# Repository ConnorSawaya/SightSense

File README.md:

# SightSense

A smart guide cane for people who are blind or have low vision. You say where you want to go ("guide me to the apple", "take me to the door"), and a small wheel at the tip of the cane steers you there while avoiding obstacles.

Built at the UCSC AI Hackathon @ SF Tech Week, October 10–11, 2026, for the ASUS Local AI track, where it placed 1st overall.

> Experimental prototype. It does not replace a white cane or a guide dog, and it has not been tested with blind users.

## See it in 3D

**[Open the interactive model and guided tour](https://connorsawaya.github.io/SightSense/)** (or click the picture): drag to turn it, step through each part, and point at a data line to see what it carries. There is more on the [project page](https://connors.dev/sightsense).

| | |
| --- | --- |
|  |  |
| **The wireless links.** Camera frames go from the phone to the GX10, guidance comes back, and one word goes to the Pi. | **The wheel end.** Battery, 5 V converter, motor driver, gearmotor and the 85 mm omni wheel. |
|  |  |
| **Pi to driver.** The six signal wires from the Pi's header to the IBT-2. | **Phone mount.** The iPhone in its tilting cradle, camera forward. |

These are pictures of a CAD model, not photos of the cane. The model was drawn on October 12, after the event, from the printable parts in [`hardware/`](hardware/) and the wiring in [`hardware/wiring.md`](hardware/wiring.md). The bought parts in it are drawn from published sizes, not measured, and where the motor driver, converter and adapter sit is made up: no mount is designed for them yet. It shows three tubes; [`hardware/assembly/`](hardware/assembly/) draws four.

## Photos from the event

Taken by the team at the event.

| | |
| --- | --- |
|  |  |
| The cane at the event, with the wheel end on the floor. | The team: Viraj Rungta, Aryan Kulkarni and Connor Sawaya. Not pictured: Anshuman Kumar. The name tags were added afterwards. |

| | | | |
| --- | --- | --- | --- |
|  |  |  |  |
| The whole cane in hand: handle, phone mount and wheel. | The wheel end on the floor, with tape over the tube joints. | The Raspberry Pi in its case, the jumper wires, the green power adapter and the battery underneath. | The battery pack, the carbon tube and the omni wheel. |

## How it works

```
iPhone (on the cane)        ASUS GX10 (on the table)           Raspberry Pi (on the cane)
camera + LiDAR + position ─► obstacle check, AI models, ─────► drives the wheel motor
        ▲                    route following                    │
        └── beeps and speech ◄──────┘                           ▼
                                                          mecanum wheel
```

1. The iPhone sends a picture, a LiDAR distance map and its position about 15 times a second.
2. The GX10 checks seven directions for clear space and picks the one closest to where you want to go.
3. The GX10 sends one word to the Pi: `LEFT`, `CENTER`, `RIGHT` or `STOP`.
4. The Pi directly drives the mecanum wheel in opposite directions for LEFT/RIGHT. CENTER/STOP/FREE switch it off. If it hears nothing for 0.4 seconds, it switches the motor off.
5. A vision-language model on the GX10 finds named objects, reads signs and answers questions. It never controls the wheel.

AI and guidance run locally on the GX10. The current devices communicate through the existing Tailscale network; a private router was the original plan. Place lookup uses Apple Maps.

## Repository layout

| Folder | What goes here | Owner |
| --- | --- | --- |
| [`contracts/`](contracts/) | The agreed message formats between the phone, the GX10 and the Pi | Everyone |
| [`ios-app/`](ios-app/) | The iPhone app: capture, sending, speech, voice, maps | iPhone app |
| [`gx10/`](gx10/) | Everything that runs on the GX10: receiving frames, obstacle check, AI models, dashboard | GX10 + models, obstacle check |
| [`pi/`](pi/) | The Raspberry Pi motor controller | Cane + Pi |
| [`hardware/`](hardware/) | 3D-printable parts, wiring and build notes for the cane | Cane + Pi |
| [`docs/`](docs/) | Project history, tool disclosure and supporting notes | Team lead |

## Hardware

- iPhone 16 Pro (camera, LiDAR, ARKit)
- ASUS Ascent GX10 (borrowed from ASUS for the event)
- Raspberry Pi 5
- 12 V 120 rpm DC worm gear motor driving an 85 mm omni wheel, IBT-2 (BTS7960) motor driver. Older notes here call it the mecanum wheel
- 12 V 3 Ah battery pack, fuse, kill switch
- 18 mm carbon-fibre tube cane with a printed keyed coupler (see [`hardware/cane-coupler/`](hardware/cane-coupler/))

The full list, down to the screws, is in [`hardware/BOM.md`](hardware/BOM.md).

## Status

**Since the hackathon (October 14):** the GX10 was borrowed for the event and is no longer part of the plan. The iPhone will run the obstacle check itself, a new circuit board on the cane ([`hardware/cane-board/`](hardware/cane-board/)) replaces the Raspberry Pi and takes commands from the phone over Bluetooth, and the talk button's questions will go to a cloud AI. None of that is built yet; the rest of this page describes the cane as it was at the event.

The iPhone and GX10 application code is in. The Pi has direct wheel mode and a one-time SD installer. Software tests use synthetic phone frames, real local WebSockets and mock GPIO. Actual wheel direction, RPM and updated Pi boot remain physical checks; see [`pi/README.md`](pi/README.md).

## Team

Connor Sawaya, Viraj Rungta, Aryan Kulkarni and Anshuman Kumar.

Roles to be added by the team.

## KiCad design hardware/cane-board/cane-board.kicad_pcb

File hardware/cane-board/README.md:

# Cane board (v0.1)

One circuit board for the cane, to replace the Raspberry Pi 5, its 12 V to 5 V converter, the IBT-2 motor driver, the green screw adapter and the jumper wires. The battery, the motor, the talk button and the kill switch stay off the board and plug into it.

A design, not a finished board. The schematic is drawn and checked, and the 46 × 100 mm board is routed on 4 layers with black solder mask: KiCad's design rules check reports 0 errors and 0 unconnected items, and the board matches the schematic. There is no firmware, and nothing has been ordered, built or tested. Drawn on October 13, 2026, after the event.

The thinking stays off the board. Since October 14 the plan is for the iPhone to run the obstacle check, with no GX10. The board does the Pi's job: it holds a Bluetooth LE link to the phone, turns `LEFT`, `CENTER`, `RIGHT`, `STOP` and `FREE` into motor power, sends the talk button's presses to the phone and reports its health. The commands are the same words as in [`../../contracts/MESSAGES.md`](../../contracts/MESSAGES.md); the Bluetooth format for them is not written yet. Nothing on the board changes for Bluetooth: the ESP32-S3 has it built in.

## What is on it

| Block | Main part | What it does |
| --- | --- | --- |
| Battery in | Barrel jack, resettable fuse that holds 4 A, two AO3401A | Takes the pack's barrel plug. Stays off if the plug is wired the other way round |
| Motor supply | AO3401A | Feeds the motor driver only while the kill-switch loop is closed |
| Motor driver | DRV8876 | Replaces the IBT-2. 3.5 A peak, with a current limit set by one resistor and a current reading for the processor |
| 12 V to 5 V | YLPTEC K7805-1000R3 | A sealed ready-made converter module, soldered in. 1 A, 8 to 36 V in. Chosen over a converter built from parts because its layout is done inside the module |
| 3.3 V | AP2112K-3.3 | Supply for the processor, from the 5 V rail or from the firmware socket. The power switch turns this regulator off |
| Processor | ESP32-S3-WROOM-1-N4 | Replaces the Raspberry Pi. Wi-Fi, two cores, USB built in, 4 MB of flash. No SD card, no operating system |
| Phone socket | TPS2069C, USB-C | Not fitted. Pads only. The 1 A module is too small to feed it; fitting it later needs a bigger converter |
| Firmware socket | USB-C | Loads firmware straight into the processor. Also runs the processor on a desk with no battery |
| Spare | Headers | Wheel encoder (RPM is unmeasured today), I2C, a small buzzer motor for the handle, serial |

## The board

46 × 100 mm, four layers, black solder mask, every part on the top side. Tracks on all four layers with ground poured round them and tied together by about 260 vias. The battery, motor-supply and motor tracks are drawn by hand in `make_route.py`, 0.6 to 1.0 mm wide on the outer layers, and the Freerouting autorouter routes everything else around them. The top edge points up the cane.

- **Top:** the processor, with its aerial along the top edge and nothing beside it. Kill switch, talk button and buzzer plugs on the left, where the wires from the handle arrive. Firmware socket on the right edge.
- **Middle:** 3.3 V, the 12 V to 5 V module, the power switch on the right edge, and the unfitted phone socket's pads.
- **Bottom:** battery jack and motor XT30 socket on the bottom edge, with the fuse, the two protection FETs and the motor driver just above them. The two motor tracks run straight down the underside from the driver to the XT30. Encoder plug on the left.
- Four M3 holes: two just below the processor and two at the bottom corners.

In the pictures four parts are stand-ins of the same kind and size, because KiCad ships no 3D model for the ones chosen: the firmware socket, the two push buttons and the slide switch. The fuse and the XT30 have no model and show as bare pads. The bare pads on the right are the phone socket.

### Checks on the routed board, October 14

- KiCad's design rules check: 0 errors, 0 unconnected items. The board matches the schematic (the only differences are unused pins and part descriptions).
- No copper under the processor's aerial on any of the four layers.
- Battery, motor and 5 V tracks run only on the outer layers.
- Narrowest copper on each motor-current path, pad to pad, checked by script: battery jack to fuse 1.0 mm; fuse to the protection FETs 0.6 mm; FETs to the kill-switch FET 0.8 to 1.0 mm; kill-switch FET to the driver 0.6 to 1.0 mm, then 0.4 mm for the last 1.4 mm into the pin; driver to the XT30 1.0 mm, with 0.4 mm for about 1 mm at each pin. The driver's pins are 0.3 mm wide, so the copper can not be wider there.
- By the IPC-2221 rule of thumb, a 0.4 mm outer track holding 2.2 A all the time would warm by about 35 °C; at the 0.4 to 0.6 A the motor usually takes, about 2 °C. These runs are short and next to large copper, so the real figure should be lower. Estimates, not measurements.
- Ordering files: `export/fab/` holds the Gerbers and drill files zipped for upload, JLCPCB's placement file and the BOM. `export/fab-other/` holds the same board for other assemblers (PCBWay and the like): a BOM by maker's part number, a placement file in KiCad's rotations, and a top assembly drawing. Made by `make_fab.py`.

## Three ways the motor is switched off

None of these depends on the firmware being right.

1. **Kill switch.** A switch on connector J3 holds the motor supply on. Open the switch, unplug it or break a wire, and the motor supply is off, by my sums within about 2 ms. The processor cannot override it. The switch carries about 0.5 mA, so it can be small and its wires thin.
2. **Watchdog.** The driver is awake only while the processor keeps toggling one pin. If the firmware hangs or the processor resets, the driver sleeps: in about 60 ms if the pin stops low, about 125 ms if it stops high (`check_watchdog.py`). Solder jumper JP1 bypasses this if it misbehaves.
3. **Current limit.** R5 sets the motor's current limit: 3.3 V ÷ R5 ÷ 0.001. With 1.5 kΩ that is 2.2 A, set above the 1.0 to 1.7 A stall currents in seller tables so the motor pushes as hard as it did on the IBT-2. That is the steady figure: for about the first millisecond of a pulse, the empty filter capacitor C7 draws on IPROPI through R6 and lets the current reach about 2.5 A (an outside review's estimate). The motor's inductance and the driver's timing set the real peaks; measure them. The IBT-2 has no such limit. Lower it once the stall current is measured.

The firmware still has to keep the rules in `AGENTS.md`: off when a command's time-to-live runs out, off after 0.4 s of silence, and no motor power taken from the network.

### Rules for the firmware

The board's protection assumes these. Each comes from an item in [`POTENTIAL_PROBLEMS.md`](POTENTIAL_PROBLEMS.md).

1. **Toggle HBEAT from the main control loop, as a 200 Hz square wave or faster** (400 toggles a second), and only when the loop has run all the way through. Never from a hardware timer or PWM, which keeps running when the program hangs. `check_watchdog.py` puts nSLEEP at 2.5 V at 200 Hz, 2.2 V at 100 Hz, and below the driver's 1.5 V threshold under about 40 Hz. The driver sleeps about 60 ms after the toggling stops with the pin low, and about 125 ms if it is left high, so the firmware's own stop leaves it low (items 12 and 27).
2. **Stop driving the motor when VBAT_ADC reads under 9.3 V**, and say "battery low" before that. The dividers and their capacitors settle with a 9 ms time constant, so ignore the readings for the first 100 ms after power-up, and calibrate them: battery volts are about 11 times the pin's. Below about 8 V at the jack the 5 V module drops out and the processor resets (item 31).
3. **Back off on a stall.** Read I_ADC with 12 dB attenuation: Espressif characterises that range to 2.9 V, about 1.93 A at 1.5 V per amp, so treat anything above it as high current. When it stays high for longer than a pulse, stop and wait. At the 2.2 A limit the driver makes about 3.4 W and its own over-temperature cut-out will stop it anyway (item 22).
4. **Treat nFAULT low as "motor off until it clears".** It reports overcurrent, undervoltage and over-temperature, not the normal 2.2 A chopping (item 28).
5. **Arm in order.** At boot set MOT_EN, HBEAT and the buzzer low before anything else. Start the heartbeat, then keep MOT_EN low for about 15 ms before driving. The model fills the pump in under 1 ms and the driver wakes in 1 ms, but capacitor tolerances can slow the pump several times over (an outside review). The driver's inputs are pulled down and the pump is empty at power-up, so this is belt and braces.
6. **Disarm at once.** On a stale command, a lost link or any fault: MOT_EN low straight away, heartbeat stopped low, and wait for a fresh command after re-arming.

The kill switch does not protect against its two wires shorting together. That reads as "switch closed".

**Brake or coast.** With PMODE on ground the driver runs in PH/EN mode. When the firmware turns the motor off, the driver brakes it (both low-side switches on); when the driver sleeps, through the watchdog or a hang, the motor coasts. The IBT-2 on the Pi coasted, because the Pi switched its enables off. The motor's worm gear holds the wheel either way, so the two differ only in the last few milliseconds of spin-down, and a brake ends each pulse sooner. Decided on October 14 to keep it. Firmware that wants a coast for `FREE` stops toggling the heartbeat low, and the driver sleeps within about 60 ms.

## Will it run for three hours?

By these sums, yes, with a lot to spare. The phone is not powered from the board: the decision on October 13 was to leave the phone socket's parts off.

Every figure here is an estimate. Nothing was measured.

| What | Power from the battery | How I got it |
| --- | --- | --- |
| Processor, lights, standby | About 0.8 W | 120 mA at 3.3 V assumed with Wi-Fi held open. Espressif gives 95 mA receiving and 355 mA peaks sending, but no average |
| Motor, typical | About 1.3 W | Assumes the wheel drives 30% of the time at 0.4 A |
| Motor, driving all the time | About 6.6 W | 0.6 A, the highest rated current in the seller tables |
| Phone socket at full rate, if it is ever fitted | About 8.5 W | 7.5 W at the socket, plus converter loss |

The pack is labelled 12 V 3 Ah, about 32 Wh. I counted 26 Wh as usable. Its capacity has not been checked under load.

| Case | Power | Runs for |
| --- | --- | --- |
| Typical | 2.1 W | About 12 hours |
| Wheel driving all the time | 7.4 W | About 3.5 hours |
| If the socket is fitted: typical, and the phone taking 4.5 W | 7.2 W | About 3.5 hours |
| If the socket is fitted: typical, and the phone taking the full 7.5 W | 10.6 W | About 2.5 hours |

- The Raspberry Pi 5 idles at about 3 W with Wi-Fi on, so the processor's share drops to roughly a quarter.
- The phone runs on its own battery, about 13.6 to 13.9 Wh, and is likely to run out before the cane does. How much the app draws is not measured.
- The socket can no longer be fitted as it is: the 1 A module is too small for it, so a bigger converter would be needed first. If that is done, a 5 Ah pack of the same kind would cover every row above. Whether an iPhone takes 1.5 A from it is not confirmed; the socket advertises 1.5 A the standard way, with 22 kΩ on each CC pin.

## Currents against the parts' ratings

| Path | Most it can carry by design | Part's rating |
| --- | --- | --- |
| Battery jack, fuse, reverse-plug FETs | About 2.5 A: motor at its 2.2 A limit and the processor's peaks, on a 9 V pack | Jack 5 A, fuse holds 4 A, two FETs of 4 A each side by side |
| Kill-switch FET | 2.2 A, the motor's limit. About 0.3 W of heat then, an estimated 35 °C rise. R2 and R3 hold its gate at 0.43 of the battery: 3.9 V from a flat 9 V pack, 10.6 V at the protection diode's clamp | 4 A |
| Motor driver | 2.2 A, set by R5 | 3.5 A peak |
| 5 V rail | About 0.5 A, the processor's peaks | 1 A |
| 3.3 V rail | About 0.44 A: 355 mA Wi-Fi peak and an 80 mA buzzer | 0.6 A |

- The motor's stall current is 1.0 to 1.7 A in seller tables for JGY-370 motors. None of those tables is for the team's motor. Measure it, then choose R5.
- A stalled motor at 1.7 A makes the driver turn about 2 W into heat (0.7 Ω, two switches in series); at the 2.2 A limit, about 3.4 W. Either is too hot to last; the driver's own over-temperature cut-out switches it off, and the firmware should stop on a stall. At 0.4 to 0.6 A it is 0.1 to 0.25 W.
- On the Pi the IBT-2 ran the motor at 70 to 100% power with no limit at all, so the 2.2 A limit should not take away push the motor had.

## Processor pins

| ESP32 pin | Net | Job |
| --- | --- | --- |
| IO1 | `I_ADC` | Motor current, 1.5 V per amp with R5 at 1.5 kΩ. Reads up to about 2 A |
| IO2 | `VBAT_ADC` | Battery voltage ÷ 11 (1M and 100k): 1.15 V at a full pack |
| IO4 | `VM_ADC` | Motor supply ÷ 11. Tells the firmware whether the kill switch is closed |
| IO5 | `MOT_EN` | Motor power (PWM) |
| IO6 | `MOT_PH` | Motor direction |
| IO7 | `HBEAT` | Watchdog: must keep toggling |
| IO8, IO9 | `SDA`, `SCL` | I2C header |
| IO10 | `HAPTIC` | Buzzer motor |
| IO11 | `PH_EN` | Phone socket on (high) or off. Spare while the socket is not fitted |
| IO12 | `PH_FLT` | Phone socket overloaded (low). Spare while the socket is not fitted |
| IO13, IO14 | `ENC_A`, `ENC_B` | Encoder header |
| IO15 | `DRV_FLT` | Motor driver fault (low) |
| IO16 | `TALK` | Talk button (low when pressed) |
| IO21 | `LED_ST` | Status light |
| IO19, IO20 | `USB_DN`, `USB_DP` | Firmware socket |

The current, battery and motor-supply readings use ADC1, which works with Wi-Fi on. The motor pins only glitch low at power-up, by Espressif's table, and the driver is asleep then anyway.

## Connectors

| Ref | For | Type |
| --- | --- | --- |
| J1 | Battery | Barrel jack for a 5.5 mm plug, 2.0 mm pin. Measure the pack's plug before ordering: a 2.5 mm plug will be loose, and the same jack comes with a 2.5 mm pin |
| J2 | Motor | XT30 socket, upright. Solder the motor wires to a matching XT30 plug; nothing is soldered to the board. Which wire goes to which pin only sets the wheel's direction, which the firmware can swap, as `--swap` does on the Pi |
| J3 | Kill switch | JST XH, 2 way. Fit a jumper if there is no switch |
| J4 | Talk button | JST XH, 2 way. The 10 kΩ pull-up `wiring.md` suggests for a long wire is on the board |
| J5 | Wheel encoder | JST XH, 4 way: 3.3 V, ground, A, B |
| J6 | I2C | Pin header, 4 way |
| J7 | Buzzer motor | JST XH, 2 way, 3.3 V |
| J8 | Serial | Pin header, 3 way |
| J10 | Phone power | USB-C, power only. Not fitted |
| J11 | Firmware | USB-C |

## Cost

[`BOM.md`](BOM.md) has every line with its order code, price and JLCPCB class, read from JLCPCB's parts library on October 13, 2026.

- Parts for one board: $10.48. The processor module is $4.13 of that.
- Five boards made and assembled by JLCPCB, 4 layers, black: $107.31 before shipping, duty and tax; about $172 delivered with the 35% tariff, so about $34 a board. See [`COST.md`](COST.md).
- The BOM lists the changes that cut the cost and what each one changed in the design.
- Bench-test parts to buy first: a DRV8876 breakout at $8.15 and an ESP32-S3 dev board at about $15 to $20.
- Not priced: the kill switch and the plug leads.

What the board replaces is not priced in this repository. My guess for a Raspberry Pi 5 with cooler, case and card, the converter and the IBT-2 is $100 to $120.

## Files

| File | What it is |
| --- | --- |
| `make_board.py` | Lists every part and the net on every pin, draws the schematic from that, and checks it. Standard-library Python; needs KiCad 10 |
| `cane-board.kicad_sch`, `cane-board.kicad_pro` | The KiCad 10 project. Open it in KiCad to look or to carry on by hand |
| `cane-board.kicad_sym`, `sym-lib-table` | The DRV8876 symbol, which KiCad does not ship |
| `make_pcb.py` | Places every part on the board from a table of positions, joins the pads to their nets, runs KiCad's design rules check and renders the 3D pictures. Run it with the Python inside KiCad |
| `make_route.py` | Lays the hand-drawn power tracks, runs the Freerouting autorouter for the rest, widens what it can, pours and stitches ground, makes the board black and runs the design rules check. Needs Java and the Freerouting jar in `FREEROUTING_JAR` |
| `make_fab.py` | Writes the ordering files in `export/fab/` and `export/fab-other/`. JLCPCB's placement file has each part's pad centre and JLCPCB's rotation, checked part by part and in JLCPCB's placement viewer. Run it with the Python inside KiCad |
| `check_watchdog.py` | Simulates the watchdog pump: nSLEEP voltage against the heartbeat rate, and the time to sleep. Standard-library Python |
| `cane-board.kicad_pcb` | The routed board |
| `export/cane-board.pdf` | The schematic to read or print |
| [`BOM.md`](BOM.md) | What to buy, with order codes and prices, and what the board lets you drop |
| `export/parts.csv` | The board's parts grouped into lines to buy |
| `export/bom-jlcpcb.csv` | The fitted parts in the columns JLCPCB's assembly order form reads |
| `previews/cane-board.png` | Picture of the PDF, made separately |
| `previews/board-*.png` | 3D pictures of the board, rendered by KiCad |

`python3 make_board.py` rewrites the schematic, so edits made in KiCad are lost. Either change the script, or stop running it once the schematic is being drawn by hand.

Schematic checks on the last run, October 14: 256 pins on 56 nets all on the net the script lists, as read back from KiCad's own netlist; every pin has a matching pad on its footprint; KiCad's electrical rules check reports 0 errors and 0 warnings. These show the drawing matches the list. They do not show the circuit works.

## Not done

- **The link.** Decided October 14: Bluetooth LE from the phone, so no Wi-Fi network or Tailscale is needed (an ESP32 cannot run Tailscale). The message format over it is not written; it belongs in `contracts/MESSAGES.md`, which needs Connor's say-so.
- **Firmware.** Not started. Arduino / PlatformIO (decided October 14). It has to do what `pi/cane.py` and `pi/wheel_drive.py` do, with the same limits and tests run against fakes, plus the rules above.
- **A new electronics mount** for the 46 × 100 mm board.
- **Measurements this design leans on:** the motor's stall and running current, the battery's real capacity, the phone's draw, and the size and polarity of the pack's plug.
- **Try it on bought boards first.** An ESP32-S3 dev board and a DRV8876 breakout would prove the firmware and the motor numbers before any board is ordered.
- Small things known to be rough: the watchdog is simulated (`check_watchdog.py`) but not built, and the kill-switch timing and the gate resistors that replaced the zeners are worked out on paper only; and if the phone socket is ever fitted, it has 5 V on it whenever it is switched on, not only when a phone is attached.

## Where the facts come from

Looked up on October 13 and 14, 2026.

- DRV8876 pins, modes, current-limit formula, capacitors and land pattern: TI datasheet SLVSDS7B.
- K7805-1000R3 pins (1 in, 2 ground, 3 out), 8 to 36 V in, 1 A out: YLPTEC datasheet, read October 14.
- XT30UPB-F: AMASS drawing via KiCad's footprint and the LCSC listing C108769.
- TPS2069C enable polarity and limits: TI datasheet SLVSAU6I. AP2112K: Diodes DS39724.
- AO3401A (30 V, 4 A, gate limit ±12 V, under 85 mΩ with 2.5 V on the gate, 125 °C/W): Alpha & Omega datasheet rev. 3.1.
- Every part's price, stock and class: JLCPCB's parts library, read on October 13, 2026.
- ESP32-S3-WROOM-1 pins, boot pins, power-up glitches, ADC and currents: Espressif module datasheet v1.8 and chip datasheet v2.2.
- USB-C pull-up values: Microchip AN1953, table 6, quoting the USB Type-C specification.
- Motor currents: an OzRobotics JGY-370B table and a Seeed/Aslong sheet. No table for a 120 rpm JGY-370 could be fetched.
- Raspberry Pi 5 idle power: CNX Software's review (3.0 W headless with Wi-Fi) and Jeff Geerling's measurements (2.4 to 3.3 W).
- iPhone 16 Pro battery: 3,582 mAh from a regulatory filing reported by 9to5Mac. Apple does not publish it.
- Barrel jack (5 A, 2.0 mm pin, hole pattern): XKB's drawing for the DC-005-5A-2.0.
- Symbols and footprints other than the DRV8876: KiCad 10's own libraries.

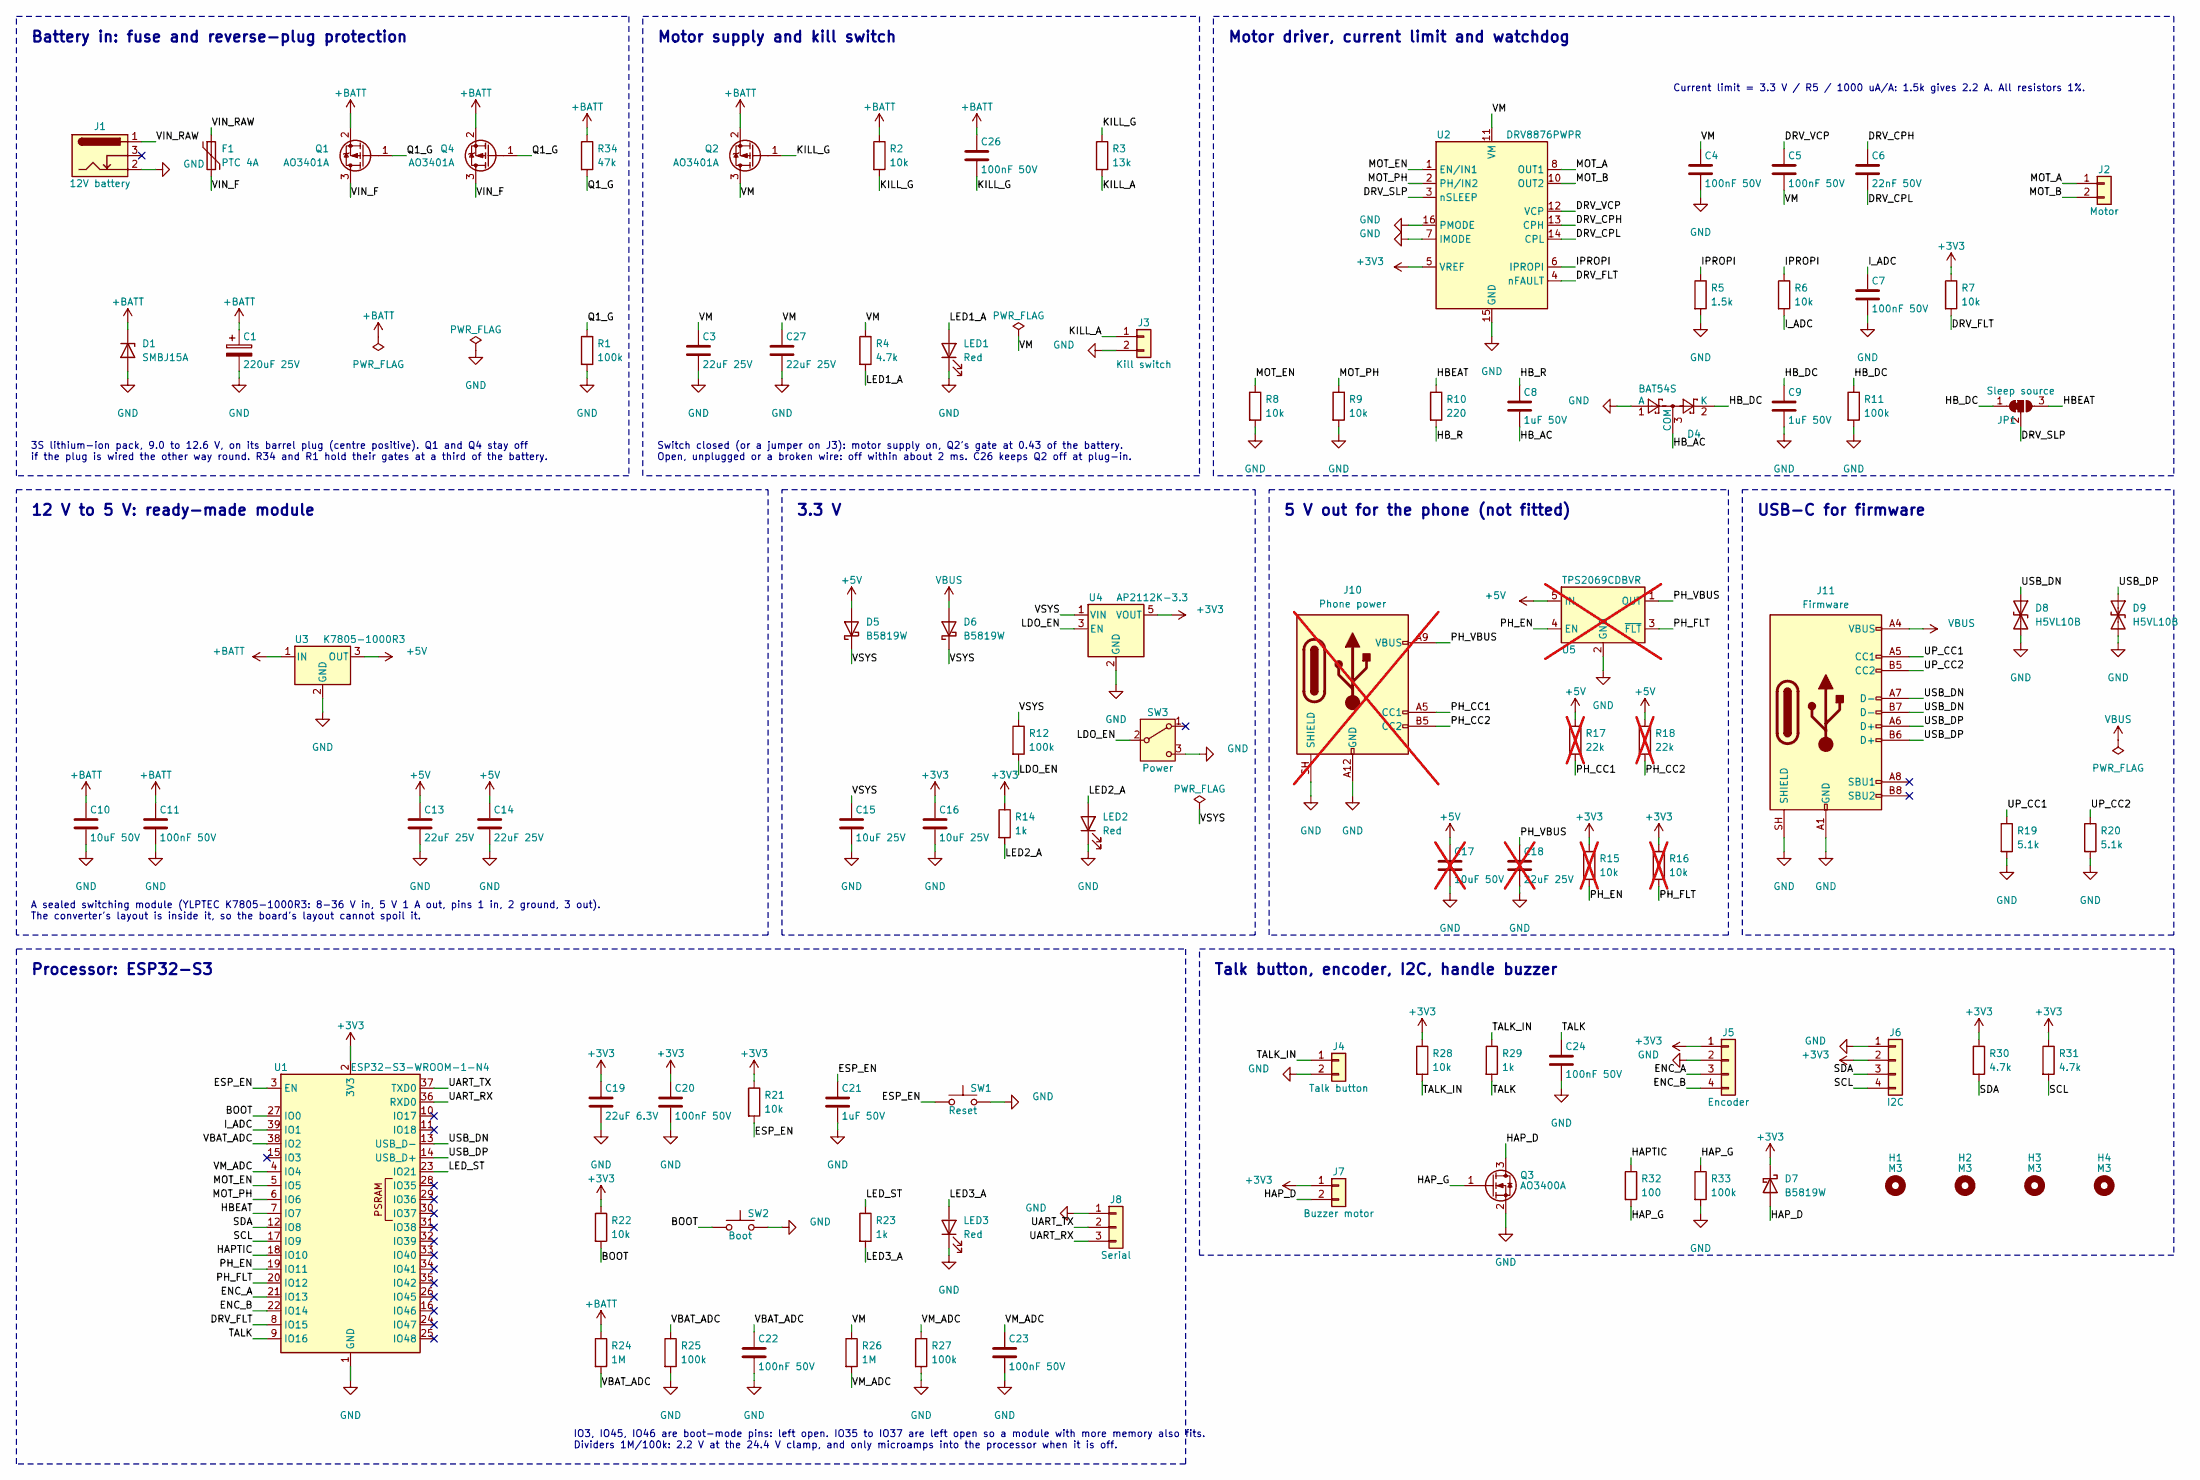
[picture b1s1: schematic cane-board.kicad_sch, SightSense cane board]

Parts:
C1: 220uF 25V; CP_Elec_8x10; MPN EMK1EM221FB0D00R; LCSC C724620
C3, C13, C14, C27: 22uF 25V; C_1206_3216Metric; MPN CL31A226KAHNNNE; LCSC C12891
C4, C5, C7, C11, C20, C22, C23, C24, C26: 100nF 50V; C_0603_1608Metric; MPN CC0603KRX7R9BB104; LCSC C14663
C6: 22nF 50V; C_0603_1608Metric; MPN CL10B223KB8NNNC; LCSC C21122
C8, C9, C21: 1uF 50V; C_0603_1608Metric; MPN CL10A105KB8NNNC; LCSC C15849
C10: 10uF 50V; C_1206_3216Metric; MPN CL31A106KBHNNNE; LCSC C13585
C15, C16: 10uF 25V; C_0805_2012Metric; MPN CL21A106KAYNNNE; LCSC C15850
C17: 10uF 50V; C_1206_3216Metric; MPN CL31A106KBHNNNE; LCSC C13585; not fitted
C18: 22uF 25V; C_1206_3216Metric; MPN CL31A226KAHNNNE; LCSC C12891; not fitted
C19: 22uF 6.3V; C_0603_1608Metric; MPN CL10A226MQ8NRNC; LCSC C59461
D1: SMBJ15A; D_SMB; MPN SMBJ15A; LCSC C19077569
D4: BAT54S; SOT-23; MPN BAT54S; LCSC C7420333
D5, D6, D7: B5819W; D_SOD-123; MPN B5819W; LCSC C8598
D8, D9: H5VL10B; D_SOD-882; MPN H5VL10B; LCSC C7420372
F1: PTC 4A; Fuse_2920_7451Metric; MPN BSMD2920-400-30V; LCSC C20539726
H1, H2, H3, H4: M3; MountingHole_3.2mm_M3
J1: 12V battery; BarrelJack_Horizontal; MPN DC-005-5A-2.0; LCSC C381116
J2: Motor; AMASS_XT30UPB-F_1x02_P5.0mm_Vertical; MPN XT30UPB-F30.G.Y; LCSC C108769
J3: Kill switch; JST_XH_B2B-XH-A_1x02_P2.50mm_Vertical; MPN B2B-XH-A; LCSC C158012
J4: Talk button; JST_XH_B2B-XH-A_1x02_P2.50mm_Vertical; MPN B2B-XH-A; LCSC C158012
J5: Encoder; JST_XH_B4B-XH-A_1x04_P2.50mm_Vertical; MPN B4B-XH-A; LCSC C144395
J6: I2C; PinHeader_1x04_P2.54mm_Vertical; MPN PZ254V-11-04P; LCSC C2691448
J7: Buzzer motor; JST_XH_B2B-XH-A_1x02_P2.50mm_Vertical; MPN B2B-XH-A; LCSC C158012
J8: Serial; PinHeader_1x03_P2.54mm_Vertical; MPN PZ254V-11-03P; LCSC C2937625
J10: Phone power; USB_C_Receptacle_GCT_USB4125-xx-x_6P_TopMnt_Horizontal; MPN USB4125-GF-A; LCSC C3151650; not fitted
J11: Firmware; USB_C_Receptacle_HRO_TYPE-C-31-M-12; MPN TYPE-C-31-M-12; LCSC C165948
JP1: Sleep source; SolderJumper-3_P1.3mm_Bridged12_RoundedPad1.0x1.5mm
LED1, LED2, LED3: Red; LED_0603_1608Metric; MPN KT-0603R; LCSC C2286
Q1, Q2, Q4: AO3401A; SOT-23; MPN AO3401A; LCSC C15127
Q3: AO3400A; SOT-23; MPN AO3400A; LCSC C20917
R1, R11, R12, R25, R27, R33: 100k; R_0603_1608Metric; MPN 0603WAF1003T5E; LCSC C25803
R2, R6, R7, R8, R9, R21, R22, R28: 10k; R_0603_1608Metric; MPN 0603WAF1002T5E; LCSC C25804
R3: 13k; R_0603_1608Metric; MPN 0603WAF1302T5E; LCSC C22797
R4, R30, R31: 4.7k; R_0603_1608Metric; MPN 0603WAF4701T5E; LCSC C23162
R5: 1.5k; R_0603_1608Metric; MPN 0603WAF1501T5E; LCSC C22843
R10: 220; R_0603_1608Metric; MPN 0603WAF2200T5E; LCSC C22962
R14, R23, R29: 1k; R_0603_1608Metric; MPN 0603WAF1001T5E; LCSC C21190
R15, R16: 10k; R_0603_1608Metric; MPN 0603WAF1002T5E; LCSC C25804; not fitted
R17, R18: 22k; R_0603_1608Metric; MPN 0603WAF2202T5E; LCSC C31850; not fitted
R19, R20: 5.1k; R_0603_1608Metric; MPN 0603WAF5101T5E; LCSC C23186
R24, R26: 1M; R_0603_1608Metric; MPN 0603WAF1004T5E; LCSC C22935
R32: 100; R_0603_1608Metric; MPN 0603WAF1000T5E; LCSC C22775
R34: 47k; R_0603_1608Metric; MPN 0603WAF4702T5E; LCSC C25819
SW1: Reset; SW_Push_1P1T_XKB_TS-1187A; MPN TS-1187A-B-A-B; LCSC C318884
SW2: Boot; SW_Push_1P1T_XKB_TS-1187A; MPN TS-1187A-B-A-B; LCSC C318884
SW3: Power; SW_SPDT_Shouhan_MSK12C02; MPN MSK12C02; LCSC C431540
U1: ESP32-S3-WROOM-1-N4; ESP32-S3-WROOM-1; MPN ESP32-S3-WROOM-1-N4; LCSC C2913197
U2: DRV8876PWPR; HTSSOP-16-1EP_4.4x5mm_P0.65mm_EP3.4x5mm_Mask3x3mm_ThermalVi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; MPN DRV8876PWPR; LCSC C575551
U3: K7805-1000R3; Converter_DCDC_RECOM_R-78E-0.5_THT; MPN K7805-1000R3; LCSC C2992391
U4: AP2112K-3.3; SOT-23-5; MPN AP2112K-3.3TRG1; LCSC C51118
U5: TPS2069CDBVR; SOT-23-5; MPN TPS2069CDBVR; LCSC C181752; not fitted

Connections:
+3V3: C16.1, C19.1, C20.1, D7.1 (K), J5.1, J6.2, J7.1, R7.1, R14.1, R15.1, R16.1, R21.1, R22.1, R28.1, R30.1, R31.1, U1.2 (3V3), U2.5 (VREF), U4.5 (VOUT)
+5V: C13.1, C14.1, C17.1, D5.2 (A), R17.1, R18.1, U3.3 (OUT), U5.5 (IN)
+BATT: C1.1, C10.1, C11.1, C26.1, D1.1 (K), Q1.2 (S), Q2.2 (S), Q4.2 (S), R2.1, R24.1, R34.1, U3.1 (IN)
/BOOT: R22.2, SW2.1, U1.27 (IO0)
/DRV_CPH: C6.1, U2.13 (CPH)
/DRV_CPL: C6.2, U2.14 (CPL)
/DRV_FLT: R7.2, U1.8 (IO15), U2.4 (nFAULT)
/DRV_SLP: JP1.2 (C), U2.3 (nSLEEP)
/DRV_VCP: C5.1, U2.12 (VCP)
/ENC_A: J5.3, U1.21 (IO13)
/ENC_B: J5.4, U1.22 (IO14)
/ESP_EN: C21.1, R21.2, SW1.1, U1.3 (EN)
/HAPTIC: R32.1, U1.18 (IO10)
/HAP_D: D7.2 (A), J7.2, Q3.3 (D)
/HAP_G: Q3.1 (G), R32.2, R33.1
/HBEAT: JP1.3 (B), R10.1, U1.7 (IO7)
/HB_AC: C8.2, D4.3 (COM)
/HB_DC: C9.1, D4.2 (K), JP1.1 (A), R11.1
/HB_R: C8.1, R10.2
/IPROPI: R5.1, R6.1, U2.6 (IPROPI)
/I_ADC: C7.1, R6.2, U1.39 (IO1)
/KILL_A: J3.1, R3.2
/KILL_G: C26.2, Q2.1 (G), R2.2, R3.1
/LDO_EN: R12.2, SW3.2 (B), U4.3 (EN)
/LED1_A: LED1.2 (A), R4.2
/LED2_A: LED2.2 (A), R14.2
/LED3_A: LED3.2 (A), R23.2
/LED_ST: R23.1, U1.23 (IO21)
/MOT_A: J2.1, U2.8 (OUT1)
/MOT_B: J2.2, U2.10 (OUT2)
/MOT_EN: R8.1, U1.5 (IO5), U2.1 (EN/IN1)
/MOT_PH: R9.1, U1.6 (IO6), U2.2 (PH/IN2)
/PH_CC1: J10.A5 (CC1), R17.2
/PH_CC2: J10.B5 (CC2), R18.2
/PH_EN: R15.2, U1.19 (IO11), U5.4 (EN)
/PH_FLT: R16.2, U1.20 (IO12), U5.3 (~FLT)
/PH_VBUS: C18.1, J10.A9 (VBUS), J10.B9 (VBUS), U5.1 (OUT)
/Q1_G: Q1.1 (G), Q4.1 (G), R1.1, R34.2
/SCL: J6.4, R31.2, U1.17 (IO9)
/SDA: J6.3, R30.2, U1.12 (IO8)
/TALK: C24.1, R29.2, U1.9 (IO16)
/TALK_IN: J4.1, R28.2, R29.1
/UART_RX: J8.3, U1.36 (RXD0)
/UART_TX: J8.2, U1.37 (TXD0)
/UP_CC1: J11.A5 (CC1), R19.1
/UP_CC2: J11.B5 (CC2), R20.1
/USB_DN: D8.1 (A1), J11.A7 (D-), J11.B7 (D-), U1.13 (USB_D-)
/USB_DP: D9.1 (A1), J11.A6 (D+), J11.B6 (D+), U1.14 (USB_D+)
/VBAT_ADC: C22.1, R24.2, R25.1, U1.38 (IO2)
/VIN_F: F1.2, Q1.3 (D), Q4.3 (D)
/VIN_RAW: F1.1, J1.1
/VM: C3.1, C4.1, C5.2, C27.1, Q2.3 (D), R4.1, R26.1, U2.11 (VM)
/VM_ADC: C23.1, R26.2, R27.1, U1.4 (IO4)
/VSYS: C15.1, D5.1 (K), D6.1 (K), R12.1, U4.1 (VIN)
GND: C1.2, C3.2, C4.2, C7.2, C9.2, C10.2, C11.2, C13.2, C14.2, C15.2, C16.2, C17.2, C18.2, C19.2, C20.2, C21.2, C22.2, C23.2, C24.2, C27.2, D1.2 (A), D4.1 (A), D8.2 (A2), D9.2 (A2), J1.2, J3.2, J4.2, J5.2, J6.1, J8.1, J10.A12 (GND), J10.B12 (GND), J10.SH (SHIELD), J11.A1 (GND), J11.A12 (GND), J11.B1 (GND), J11.B12 (GND), J11.SH (SHIELD), LED1.1 (K), LED2.1 (K), LED3.1 (K), Q3.2 (S), R1.2, R5.2, R8.2, R9.2, R11.2, R19.2, R20.2, R25.2, R27.2, R33.2, SW1.2, SW2.2, SW3.3 (C), U1.1 (GND), U1.40 (GND), U1.41 (GND), U2.7 (IMODE), U2.9 (PGND), U2.15 (GND), U2.16 (PMODE), U2.17 (PAD), U3.2 (GND), U4.2 (GND), U5.2 (GND)
VBUS: D6.2 (A), J11.A4 (VBUS), J11.A9 (VBUS), J11.B4 (VBUS), J11.B9 (VBUS)

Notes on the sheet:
USB-C for firmware
Motor driver, current limit and watchdog
Battery in: fuse and reverse-plug protection
Processor: ESP32-S3
Motor supply and kill switch
3.3 V
3S lithium-ion pack, 9.0 to 12.6 V, on its barrel plug (centre positive). Q1 and Q4 stay off if the plug is wired the other way round. R34 and R1 hold their gates at a third of the battery.
Switch closed (or a jumper on J3): motor supply on, Q2's gate at 0.43 of the battery. Open, unplugged or a broken wire: off within about 2 ms. C26 keeps Q2 off at plug-in.
Current limit = 3.3 V / R5 / 1000 uA/A: 1.5k gives 2.2 A. All resistors 1%.
5 V out for the phone (not fitted)
A sealed switching module (YLPTEC K7805-1000R3: 8-36 V in, 5 V 1 A out, pins 1 in, 2 ground, 3 out). The converter's layout is inside it, so the board's layout cannot spoil it.
IO3, IO45, IO46 are boot-mode pins: left open. IO35 to IO37 are left open so a module with more memory also fits. Dividers 1M/100k: 2.2 V at the 24.4 V clamp, and only microamps into the processor when it is off.
12 V to 5 V: ready-made module
Talk button, encoder, I2C, handle buzzer

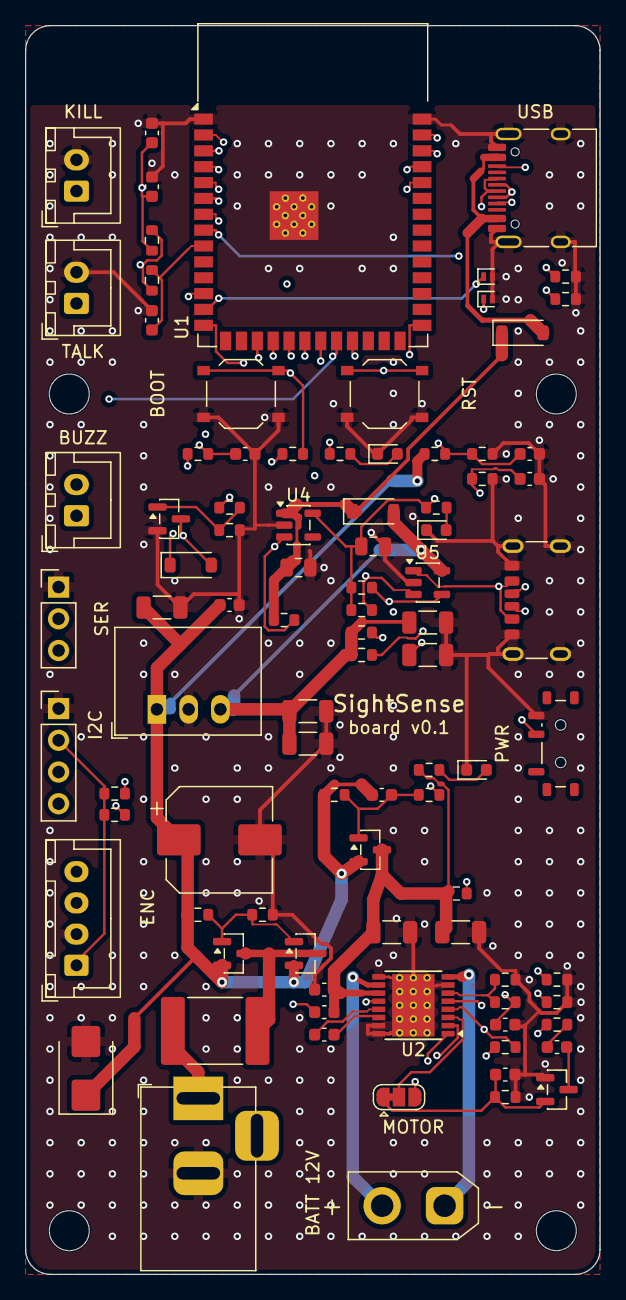
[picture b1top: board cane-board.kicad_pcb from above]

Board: 4 copper layers, 46.0 x 100.0 mm, 95 parts (0 on the bottom side), 56 nets.

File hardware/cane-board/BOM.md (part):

# Cane board: bill of materials

Everything needed to build the cane's electronics around the [cane board](README.md), and what the board lets you drop. The cane's tubes, printed parts and screws are unchanged and stay in [`../BOM.md`](../BOM.md).

Nothing here has been ordered. Order codes, prices, stock and JLCPCB's class for each part were read from JLCPCB's parts library on October 13, 2026, and will drift. Prices are US dollars for one piece, before shipping, duty and tax.

## What changes on the cane

| Item | Cane as built | With the cane board |
| --- | --- | --- |
| Raspberry Pi 5, cooler, case, microSD card | In use | Not needed: the ESP32-S3 on the board does the job |
| Converter, 12 V to 5 V | In use | Not needed: built into the board |
| Motor driver, IBT-2 | In use | Not needed: DRV8876 on the board |
| Barrel-to-screw adapter, six jumper wires | In use | Not needed: the battery plugs into the board |
| Battery, 12 V 3 Ah | In use | Keep |
| Gearmotor and omni wheel | In use | Keep. Solder the two motor wires to an XT30 plug; it plugs into the board |
| Talk button and its two wires | In use | Keep. Needs a 2-way JST XH plug on the board end |
| Kill switch | Not fitted | Buy: a switch for the handle (decided October 14). See section 4 |
| iPhone 16 Pro | In use | Keep. It runs the obstacle check and talks to the board over Bluetooth LE. It runs on its own battery |
| ASUS Ascent GX10 | Used at the hackathon, borrowed | Not needed: dropped from the plan on October 14 |
| Electronics mount (printed) | Holds the Pi and battery | Has to be redrawn for the board |

## 1. On the board

<!-- fitted: written by make_board.py -->
82 parts on 40 lines. The 40 lines with a price come to $10.48 for one board at JLCPCB's price for one piece. 7 lines (9 parts) are through-hole and cost $3.07 of that. JLCPCB classes 23 lines as Basic and 3 as Preferred, which carry no fee; 7 surface-mount lines are Extended and carry its per-line fee.

| Qty | Ref | Part | Package | Maker's number | LCSC | JLCPCB class | Each | Line |
| --- | --- | --- | --- | --- | --- | --- | --- | --- |
| 1 | U1 | ESP32-S3-WROOM-1-N4 | Module | ESP32-S3-WROOM-1-N4 | C2913197 | Extended | $4.130 | $4.13 |
| 1 | U2 | DRV8876PWPR | HTSSOP-16 | DRV8876PWPR | C575551 | Extended | $0.780 | $0.78 |
| 1 | U3 | K7805-1000R3 | Through-hole, 3 pins | K7805-1000R3 | C2992391 | Extended | $2.348 | $2.35 |
| 1 | U4 | AP2112K-3.3 | SOT-23-5 | AP2112K-3.3TRG1 | C51118 | Extended | $0.172 | $0.17 |
| 3 | Q1, Q4, Q2 | AO3401A | SOT-23 | AO3401A | C15127 | Basic | $0.102 | $0.31 |
| 1 | Q3 | AO3400A | SOT-23 | AO3400A | C20917 | Basic | $0.089 | $0.09 |
| 1 | D1 | Diode, SMBJ15A | SMB | SMBJ15A | C19077569 | Preferred | $0.055 | $0.06 |
| 1 | D4 | Diode, BAT54S | SOT-23 | BAT54S | C7420333 | Preferred | $0.014 | $0.01 |
| 3 | D5, D6, D7 | Diode, B5819W | SOD-123 | B5819W | C8598 | Basic | $0.028 | $0.08 |
| 2 | D8, D9 | Diode, H5VL10B | DFN1006 | H5VL10B | C7420372 | Preferred | $0.006 | $0.01 |
| 3 | LED1, LED2, LED3 | LED, Red | 0603 | KT-0603R | C2286 | Basic | $0.008 | $0.02 |
| 1 | F1 | Fuse, PTC 4A | 2920 | BSMD2920-400-30V | C20539726 | Extended | $0.226 | $0.23 |
| 1 | C1 | Capacitor, 220uF 25V | 8 x 10 mm can | EMK1EM221FB0D00R | C724620 | Extended | $0.114 | $0.11 |
| 4 | C3, C27, C13, C14 | Capacitor, 22uF 25V | 1206 | CL31A226KAHNNNE | C12891 | Basic | $0.128 | $0.51 |
| 1 | C6 | Capacitor, 22nF 50V | 0603 | CL10B223KB8NNNC | C21122 | Basic | $0.007 | $0.007 |
| 3 | C8, C9, C21 | Capacitor, 1uF 50V | 0603 | CL10A105KB8NNNC | C15849 | Basic | $0.016 | $0.05 |
| 1 | C10 | Capacitor, 10uF 50V | 1206 | CL31A106KBHNNNE | C13585 | Basic | $0.159 | $0.16 |
| 2 | C15, C16 | Capacitor, 10uF 25V | 0805 | CL21A106KAYNNNE | C15850 | Basic | $0.069 | $0.14 |
| 1 | C19 | Capacitor, 22uF 6.3V | 0603 | CL10A226MQ8NRNC | C59461 | Basic | $0.031 | $0.03 |
| 9 | C26, C4, C5, C7, C11, C20, C22, C23, C24 | Capacitor, 100nF 50V | 0603 | CC0603KRX7R9BB104 | C14663 | Basic | $0.014 | $0.13 |
| 6 | R1, R11, R12, R25, R27, R33 | Resistor, 1%, 100k | 0603 | 0603WAF1003T5E | C25803 | Basic | $0.003 | $0.02 |
| 8 | R2, R6, R7, R8, R9, R21, R22, R28 | Resistor, 1%, 10k | 0603 | 0603WAF1002T5E | C25804 | Basic | $0.005 | $0.04 |
| 1 | R3 | Resistor, 1%, 13k | 0603 | 0603WAF1302T5E | C22797 | Basic | $0.003 | $0.003 |
| 3 | R4, R30, R31 | Resistor, 1%, 4.7k | 0603 | 0603WAF4701T5E | C23162 | Basic | $0.003 | $0.008 |
| 1 | R5 | Resistor, 1%, 1.5k | 0603 | 0603WAF1501T5E | C22843 | Basic | $0.002 | $0.002 |
| 1 | R10 | Resistor, 1%, 220 | 0603 | 0603WAF2200T5E | C22962 | Basic | $0.004 | $0.004 |
| 3 | R14, R23, R29 | Resistor, 1%, 1k | 0603 | 0603WAF1001T5E | C21190 | Basic | $0.002 | $0.006 |
| 2 | R19, R20 | Resistor, 1%, 5.1k | 0603 | 0603WAF5101T5E | C23186 | Basic | $0.002 | $0.003 |
| 2 | R24, R26 | Resistor, 1%, 1M | 0603 | 0603WAF1004T5E | C22935 | Basic | $0.001 | $0.002 |
| 1 | R32 | Resistor, 1%, 100 | 0603 | 0603WAF1000T5E | C22775 | Basic | $0.003 | $0.003 |
| 1 | R34 | Resistor, 1%, 47k | 0603 | 0603WAF4702T5E | C25819 | Basic | $0.002 | $0.002 |
| 1 | J1 | Connector: 12V battery | Through-hole | DC-005-5A-2.0 | C381116 | Extended | $0.262 | $0.26 |
| 1 | J2 | Connector: Motor | Through-hole | XT30UPB-F30.G.Y | C108769 | Extended | $0.233 | $0.23 |
| 3 | J3, J4, J7 | Connector: Kill switch / Talk button / Buzzer motor | Through-hole | B2B-XH-A | C158012 | Extended | $0.041 | $0.12 |
| 1 | J5 | Connector: Encoder | Through-hole | B4B-XH-A | C144395 | Extended | $0.059 | $0.06 |
| 1 | J6 | Connector: I2C | Through-hole | PZ254V-11-04P | C2691448 | Extended | $0.028 | $0.03 |
| 1 | J8 | Connector: Serial | Through-hole | PZ254V-11-03P | C2937625 | Extended | $0.020 | $0.02 |
| 1 | J11 | Connector: Firmware | SMD | TYPE-C-31-M-12 | C165948 | Extended | $0.186 | $0.19 |
| 2 | SW1, SW2 | Switch: Reset / Boot | SMD, 5.1 mm square | TS-1187A-B-A-B | C318884 | Basic | $0.021 | $0.04 |
| 1 | SW3 | Switch: Power | SMD, side slider | MSK12C02 | C431540 | Extended | $0.057 | $0.06 |
<!-- end fitted -->

- This table is written by `make_board.py` from the same list that draws the schematic. `export/bom-jlcpcb.csv` holds the same lines in the columns JLCPCB's order form reads.
- Every resistor is 1%. Capacitors are X7R or X5R, except the 100 pF one, which is C0G.
- No part is needed for the four mounting holes or the solder jumper JP1.
- JLCPCB charges a fee for each Extended surface-mount line, and none for Basic or Preferred lines. Its FAQ says Preferred parts "are exempt from the Feeders Loading fee for Economic PCB assembly".

## 2. Pads on the board, parts not fitted

The 5 V socket for the phone. The pads stay on the board so it can be added later.

<!-- not fitted: written by make_board.py -->
| Qty | Ref | Part | Package | Maker's number | LCSC | JLCPCB class | Each | Line |
| --- | --- | --- | --- | --- | --- | --- | --- | --- |
| 1 | U5 | TPS2069CDBVR | SOT-23-5 | TPS2069CDBVR | C181752 | Extended | $0.137 | $0.14 |
| 1 | C17 | Capacitor, 10uF 50V | 1206 | CL31A106KBHNNNE | C13585 | Basic | $0.159 | $0.16 |
| 1 | C18 | Capacitor, 22uF 25V | 1206 | CL31A226KAHNNNE | C12891 | Basic | $0.128 | $0.13 |
| 2 | R15, R16 | Resistor, 1%, 10k | 0603 | 0603WAF1002T5E | C25804 | Basic | $0.005 | $0.01 |
| 2 | R17, R18 | Resistor, 1%, 22k | 0603 | 0603WAF2202T5E | C31850 | Basic | $0.004 | $0.008 |
| 1 | J10 | Connector: Phone power | SMD | USB4125-GF-A | C3151650 | Extended | $1.039 | $1.04 |
<!-- end not fitted -->

## 3. How the cost was cut, and what it changed

The first parts list, earlier on October 13, had 16 fee-carrying lines and cost about $11 a board. The cut-down list had 9 and cost $8.49. On October 14 the converter built from parts was swapped for a ready-made module (last row): 7 fee-carrying lines and $10.48 a board. Each change below was checked against JLCPCB's library, but none has been built.

| Change | Saves, on five boards | What it costs in the design |
| --- | --- | --- |
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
